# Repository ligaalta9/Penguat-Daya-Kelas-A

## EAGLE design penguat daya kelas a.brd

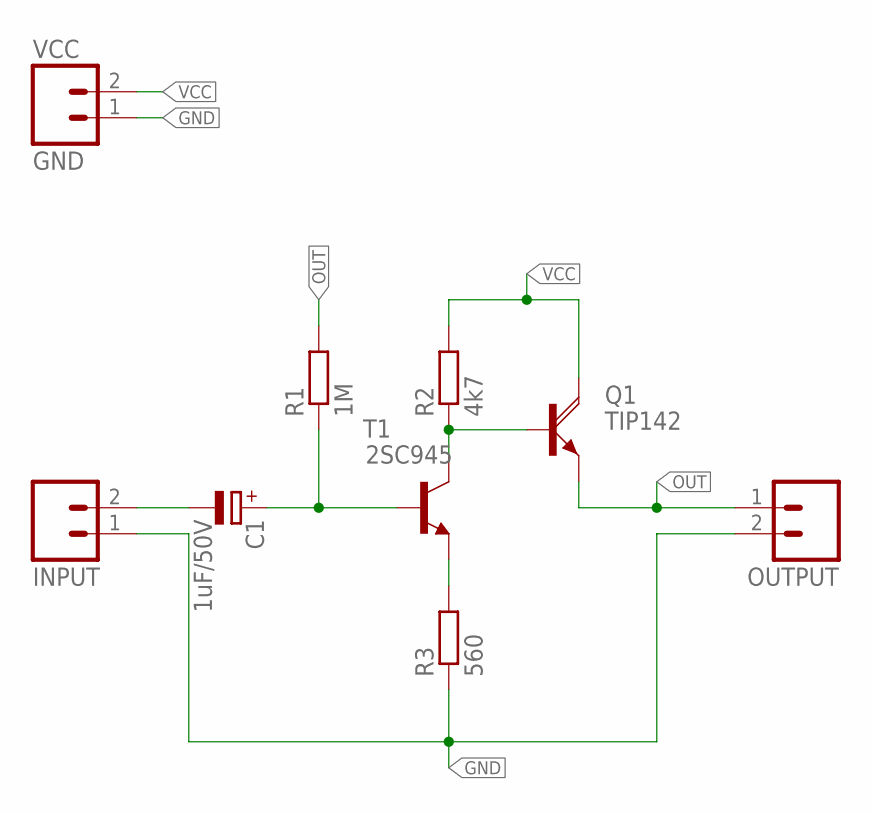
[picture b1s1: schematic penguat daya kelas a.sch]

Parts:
C1: 1uF/50V; E3,5-8
INPUT: INPUT; 02P
OUTPUT: OUTPUT; 02P
Q1: TIP142; SOT93
R1: 1M; 0204/7
R2: 4k7; 0204/7
R3: 560; 0204/7
T1: 2SC945; TO92-ECB
VCC: GND; 02P

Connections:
GND: INPUT.1, OUTPUT.2, R3.1, VCC.1
unnamed: C1.-, INPUT.2
unnamed: C1.+, R1.1, T1.B
unnamed: Q1.B, R2.1, T1.C
unnamed: R3.2, T1.E
OUT: OUTPUT.1, Q1.E, R1.2
VCC: Q1.C, R2.2, VCC.2

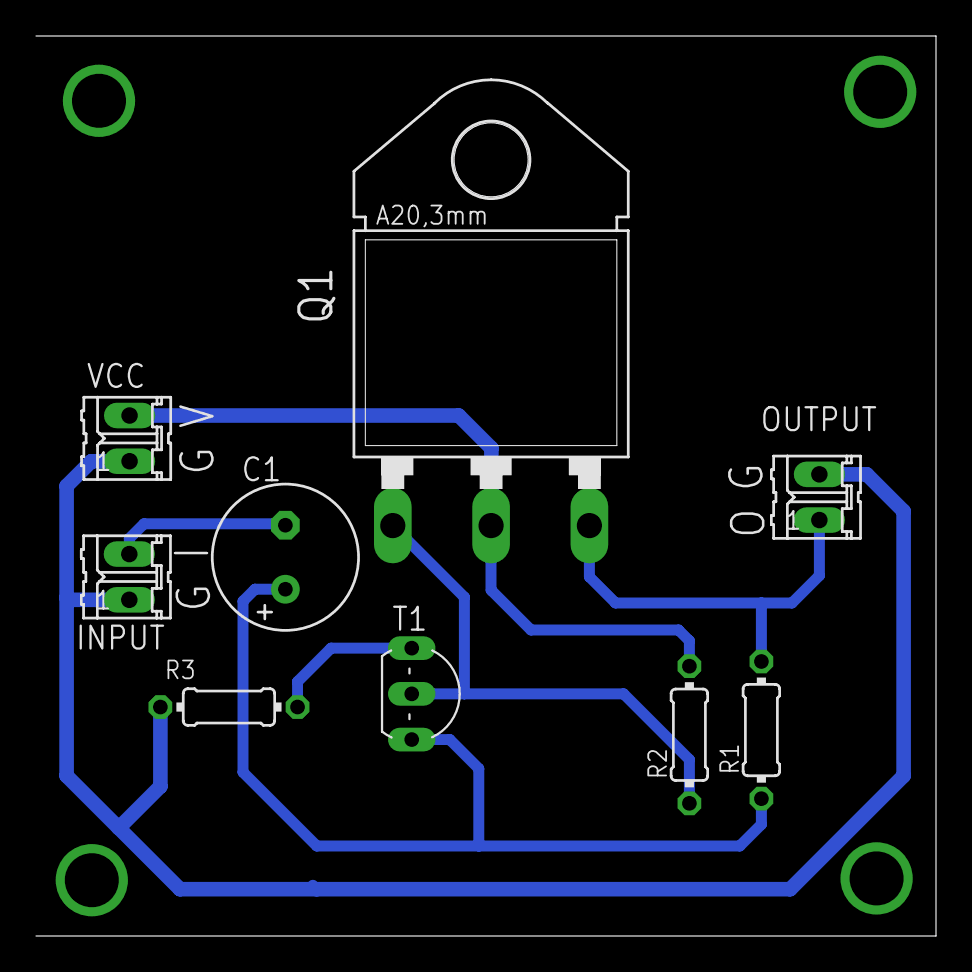
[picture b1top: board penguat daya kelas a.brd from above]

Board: 2 copper layers, 50.0 x 50.0 mm, 9 parts (0 on the bottom side), 7 nets.
